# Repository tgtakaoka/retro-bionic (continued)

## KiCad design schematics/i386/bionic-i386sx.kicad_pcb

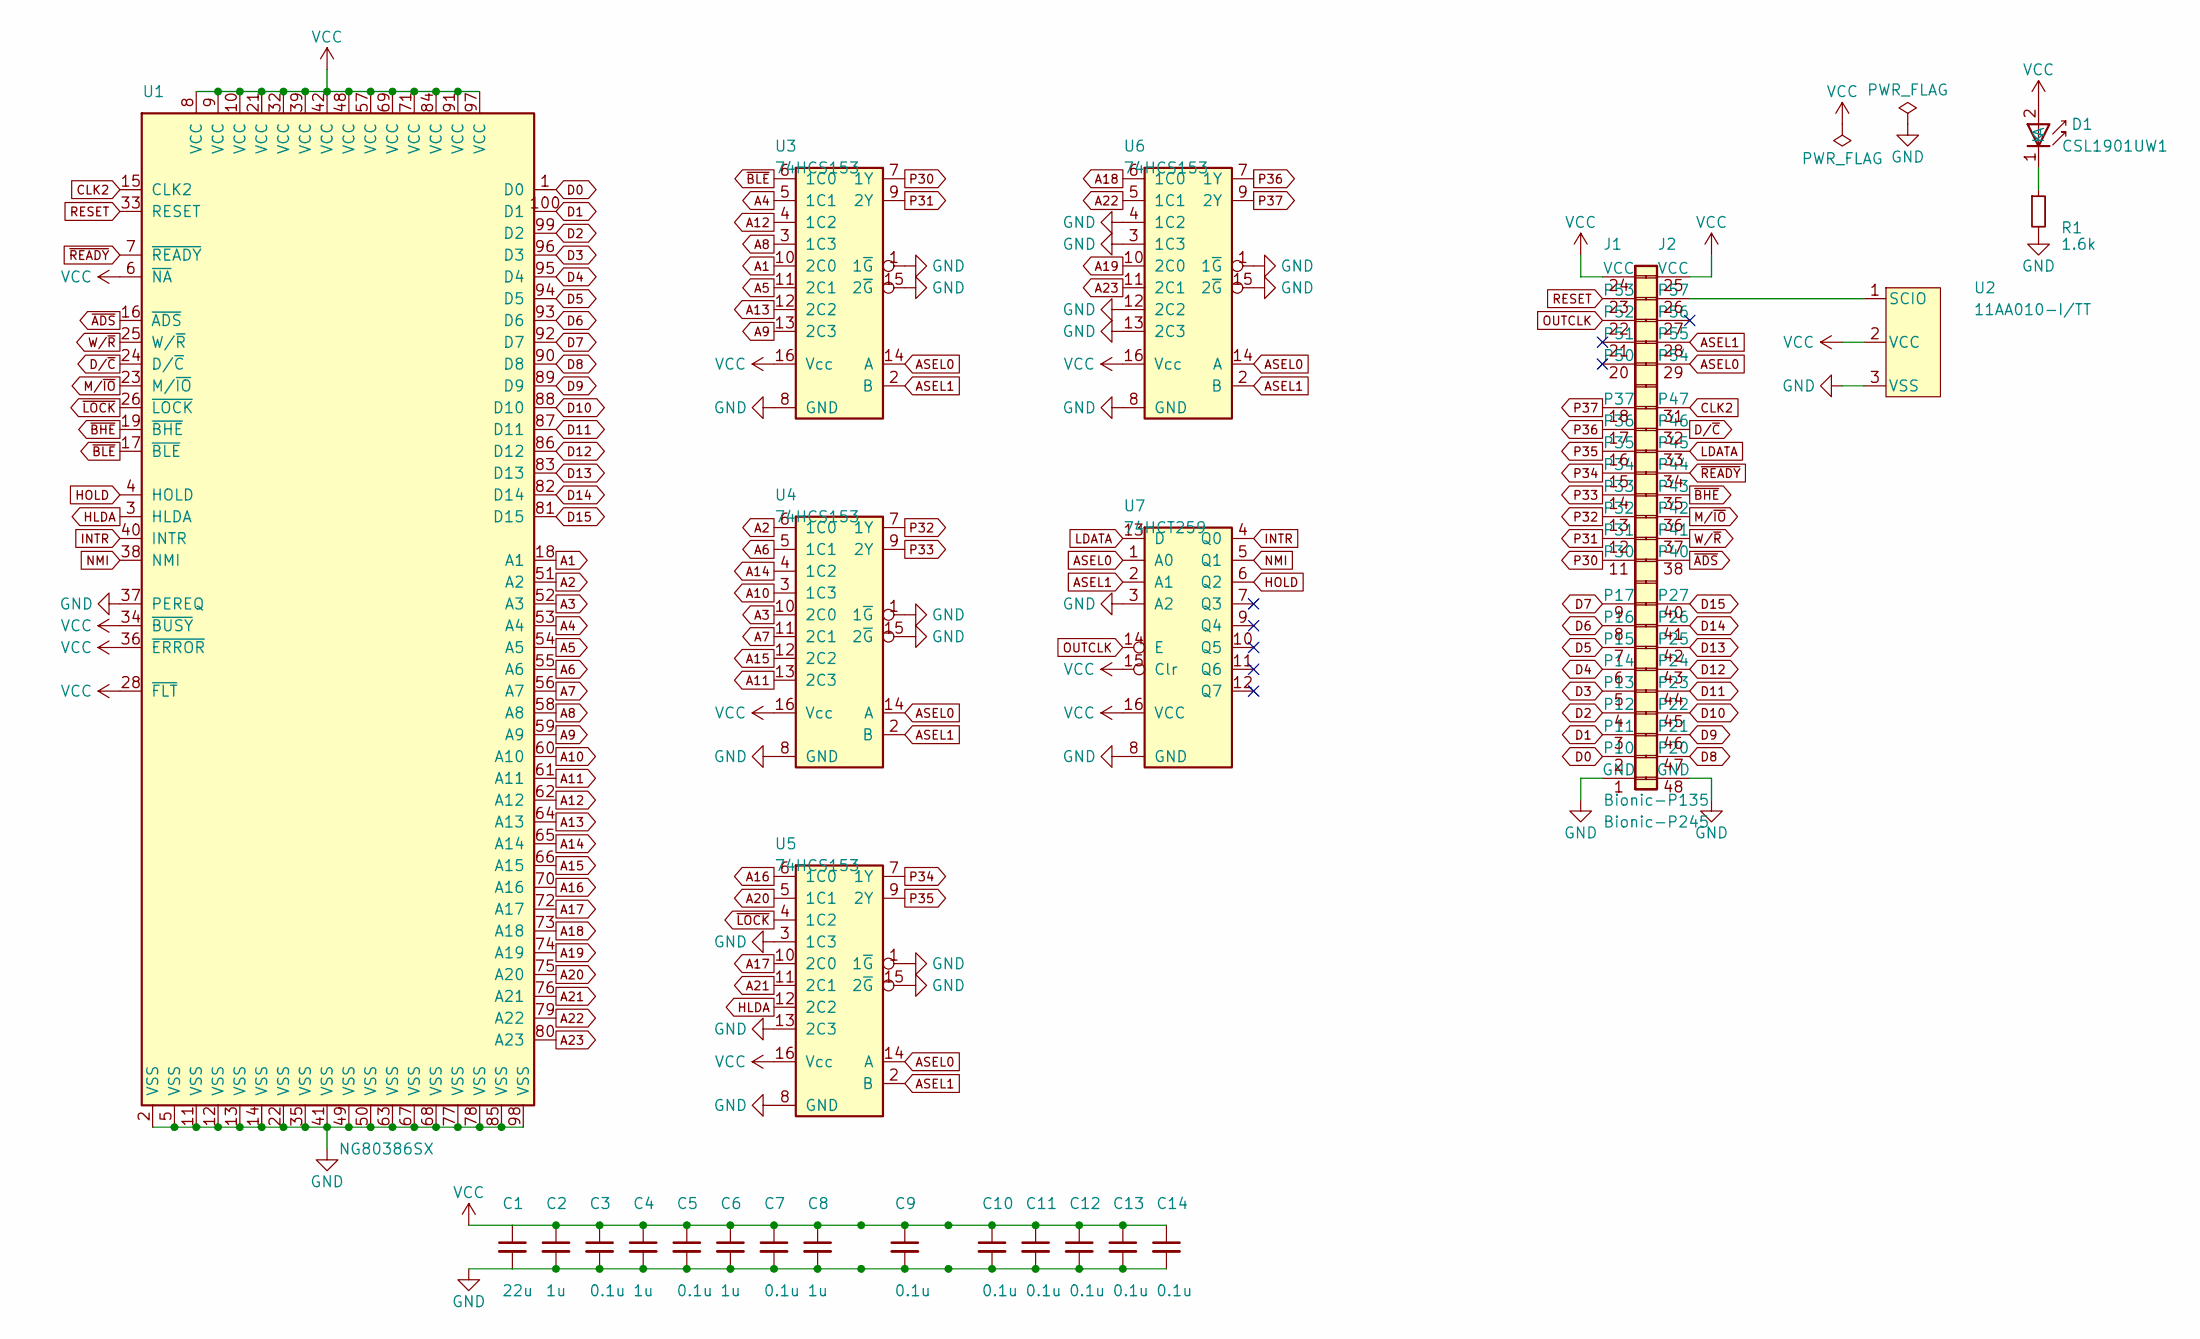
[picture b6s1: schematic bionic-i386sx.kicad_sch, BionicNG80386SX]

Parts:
C1: 22u; C_0603_1608Metric_Pad1.08x0.95mm_HandSolder
C2, C4, C6, C8: 1u; C_0603_1608Metric_Pad1.08x0.95mm_HandSolder
C3, C5, C7, C9, C10, C11, C12, C13, C14: 0.1u; C_0603_1608Metric_Pad1.08x0.95mm_HandSolder
D1: CSL1901UW1; LED_CSL1901UW1_ROM-M
J1: Bionic-P135; Bionic-P135_SMT
J2: Bionic-P245; Bionic-P245_SMT
R1: 1.6k; R_0603_1608Metric_Pad0.98x0.95mm_HandSolder
U1: NG80386SX; BQFP-100_19.05x19.05mm_P0.635mm
U2: 11AA010-I/TT; SOT-23_MC_MCH-M
U3, U4, U5, U6: 74HCS153; PW16-M
U7: 74HCT259; TSSOP16_SOT403-1_NEX-M

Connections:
A1: U1.18 (A1), U3.10 (2C0)
A2: U1.51 (A2), U4.6 (1C0)
A3: U1.52 (A3), U4.10 (2C0)
A4: U1.53 (A4), U3.5 (1C1)
A5: U1.54 (A5), U3.11 (2C1)
A6: U1.55 (A6), U4.5 (1C1)
A7: U1.56 (A7), U4.11 (2C1)
A8: U1.58 (A8), U3.3 (1C3)
A9: U1.59 (A9), U3.13 (2C3)
A10: U1.60 (A10), U4.3 (1C3)
A11: U1.61 (A11), U4.13 (2C3)
A12: U1.62 (A12), U3.4 (1C2)
A13: U1.64 (A13), U3.12 (2C2)
A14: U1.65 (A14), U4.4 (1C2)
A15: U1.66 (A15), U4.12 (2C2)
A16: U1.70 (A16), U5.6 (1C0)
A17: U1.72 (A17), U5.10 (2C0)
A18: U1.73 (A18), U6.6 (1C0)
A19: U1.74 (A19), U6.10 (2C0)
A20: U1.75 (A20), U5.5 (1C1)
A21: U1.76 (A21), U5.11 (2C1)
A22: U1.79 (A22), U6.5 (1C1)
A23: U1.80 (A23), U6.11 (2C1)
ASEL0: J2.29 (P54), U3.14 (A), U4.14 (A), U5.14 (A), U6.14 (A), U7.1 (A0)
ASEL1: J2.28 (P55), U3.2 (B), U4.2 (B), U5.2 (B), U6.2 (B), U7.2 (A1)
CLK2: J2.31 (P47), U1.15 (CLK2)
D0: J1.2 (P10), U1.1 (D0)
D1: J1.3 (P11), U1.100 (D1)
D2: J1.4 (P12), U1.99 (D2)
D3: J1.5 (P13), U1.96 (D3)
D4: J1.6 (P14), U1.95 (D4)
D5: J1.7 (P15), U1.94 (D5)
D6: J1.8 (P16), U1.93 (D6)
D7: J1.9 (P17), U1.92 (D7)
D8: J2.47 (P20), U1.90 (D8)
D9: J2.46 (P21), U1.89 (D9)
D10: J2.45 (P22), U1.88 (D10)
D11: J2.44 (P23), U1.87 (D11)
D12: J2.43 (P24), U1.86 (D12)
D13: J2.42 (P25), U1.83 (D13)
D14: J2.41 (P26), U1.82 (D14)
D15: J2.40 (P27), U1.81 (D15)
D/~C: J2.32 (P46), U1.24 (D/~C)
GND: C1.2, C2.2, C3.2, C4.2, C5.2, C6.2, C7.2, C8.2, C9.2, C10.2, C11.2, C12.2, C13.2, C14.2, J1.1 (GND), J2.48 (GND), R1.2, U1.2 (VSS), U1.5 (VSS), U1.11 (VSS), U1.12 (VSS), U1.13 (VSS), U1.14 (VSS), U1.22 (VSS), U1.35 (VSS), U1.37 (PEREQ), U1.41 (VSS), U1.49 (VSS), U1.50 (VSS), U1.63 (VSS), U1.67 (VSS), U1.68 (VSS), U1.77 (VSS), U1.78 (VSS), U1.85 (VSS), U1.98 (VSS), U2.3 (VSS), U3.1 (1~G), U3.8 (GND), U3.15 (2~G), U4.1 (1~G), U4.8 (GND), U4.15 (2~G), U5.1 (1~G), U5.3 (1C3), U5.8 (GND), U5.13 (2C3), U5.15 (2~G), U6.1 (1~G), U6.3 (1C3), U6.4 (1C2), U6.8 (GND), U6.12 (2C2), U6.13 (2C3), U6.15 (2~G), U7.3 (A2), U7.8 (GND)
HLDA: U1.3 (HLDA), U5.12 (2C2)
HOLD: U1.4 (HOLD), U7.6 (Q2)
INTR: U1.40 (INTR), U7.4 (Q0)
LDATA: J2.33 (P45), U7.13 (D)
M/~IO: J2.36 (P42), U1.23 (M/~IO)
NMI: U1.38 (NMI), U7.5 (Q1)
unnamed: D1.1 (K), R1.1
unnamed: J2.26 (P57), U2.1 (SCIO)
OUTCLK: J1.22 (P52), U7.14 (E)
P30: J1.11 (P30), U3.7 (1Y)
P31: J1.12 (P31), U3.9 (2Y)
P32: J1.13 (P32), U4.7 (1Y)
P33: J1.14 (P33), U4.9 (2Y)
P34: J1.15 (P34), U5.7 (1Y)
P35: J1.16 (P35), U5.9 (2Y)
P36: J1.17 (P36), U6.7 (1Y)
P37: J1.18 (P37), U6.9 (2Y)
RESET: J1.23 (P53), U1.33 (RESET)
VCC: C1.1, C2.1, C3.1, C4.1, C5.1, C6.1, C7.1, C8.1, C9.1, C10.1, C11.1, C12.1, C13.1, C14.1, D1.2 (A), J1.24 (VCC), J2.25 (VCC), U1.6 (~NA), U1.8 (VCC), U1.9 (VCC), U1.10 (VCC), U1.21 (VCC), U1.28 (~FLT), U1.32 (VCC), U1.34 (~BUSY), U1.36 (~ERROR), U1.39 (VCC), U1.42 (VCC), U1.48 (VCC), U1.57 (VCC), U1.69 (VCC), U1.71 (VCC), U1.84 (VCC), U1.91 (VCC), U1.97 (VCC), U2.2 (VCC), U3.16 (Vcc), U4.16 (Vcc), U5.16 (Vcc), U6.16 (Vcc), U7.15 (Clr), U7.16 (VCC)
W/~R: J2.37 (P41), U1.25 (W/~R)
~ADS: J2.38 (P40), U1.16 (~ADS)
~BHE: J2.35 (P43), U1.19 (~BHE)
~BLE: U1.17 (~BLE), U3.6 (1C0)
~LOCK: U1.26 (~LOCK), U5.4 (1C2)
~READY: J2.34 (P44), U1.7 (~READY)

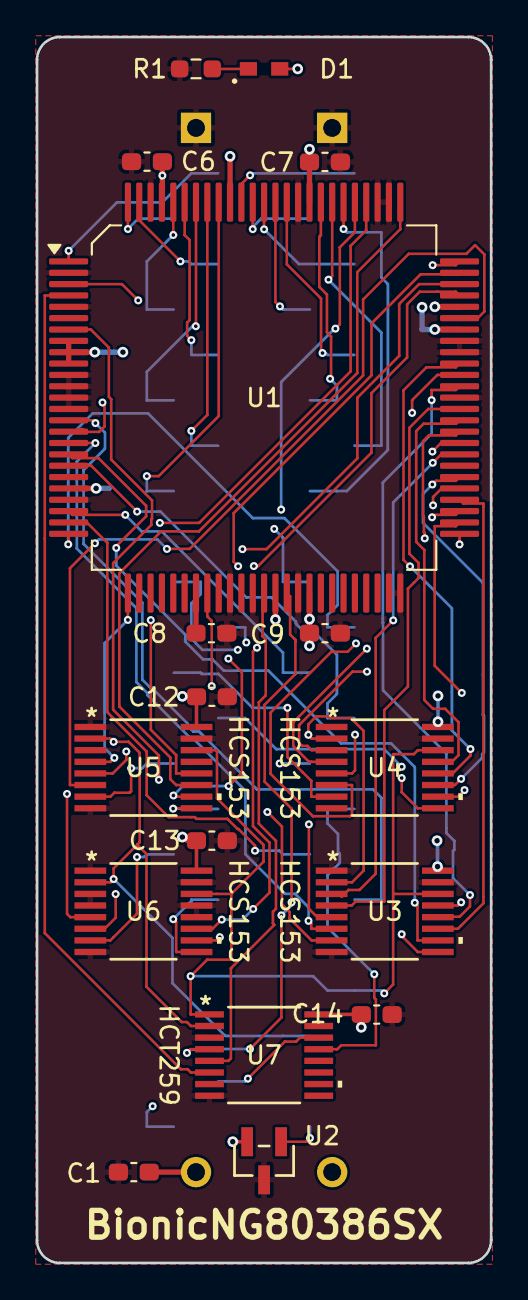
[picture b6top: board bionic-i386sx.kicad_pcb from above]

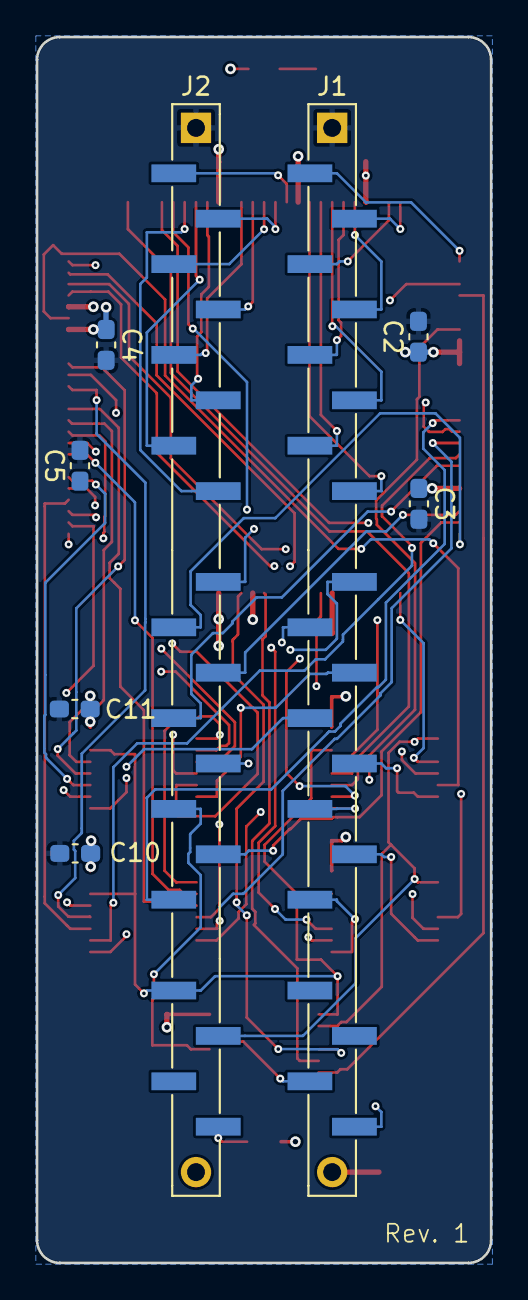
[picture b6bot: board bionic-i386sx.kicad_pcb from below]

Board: 4 copper layers, 25.4 x 68.6 mm, 25 parts (8 on the bottom side), 69 nets.

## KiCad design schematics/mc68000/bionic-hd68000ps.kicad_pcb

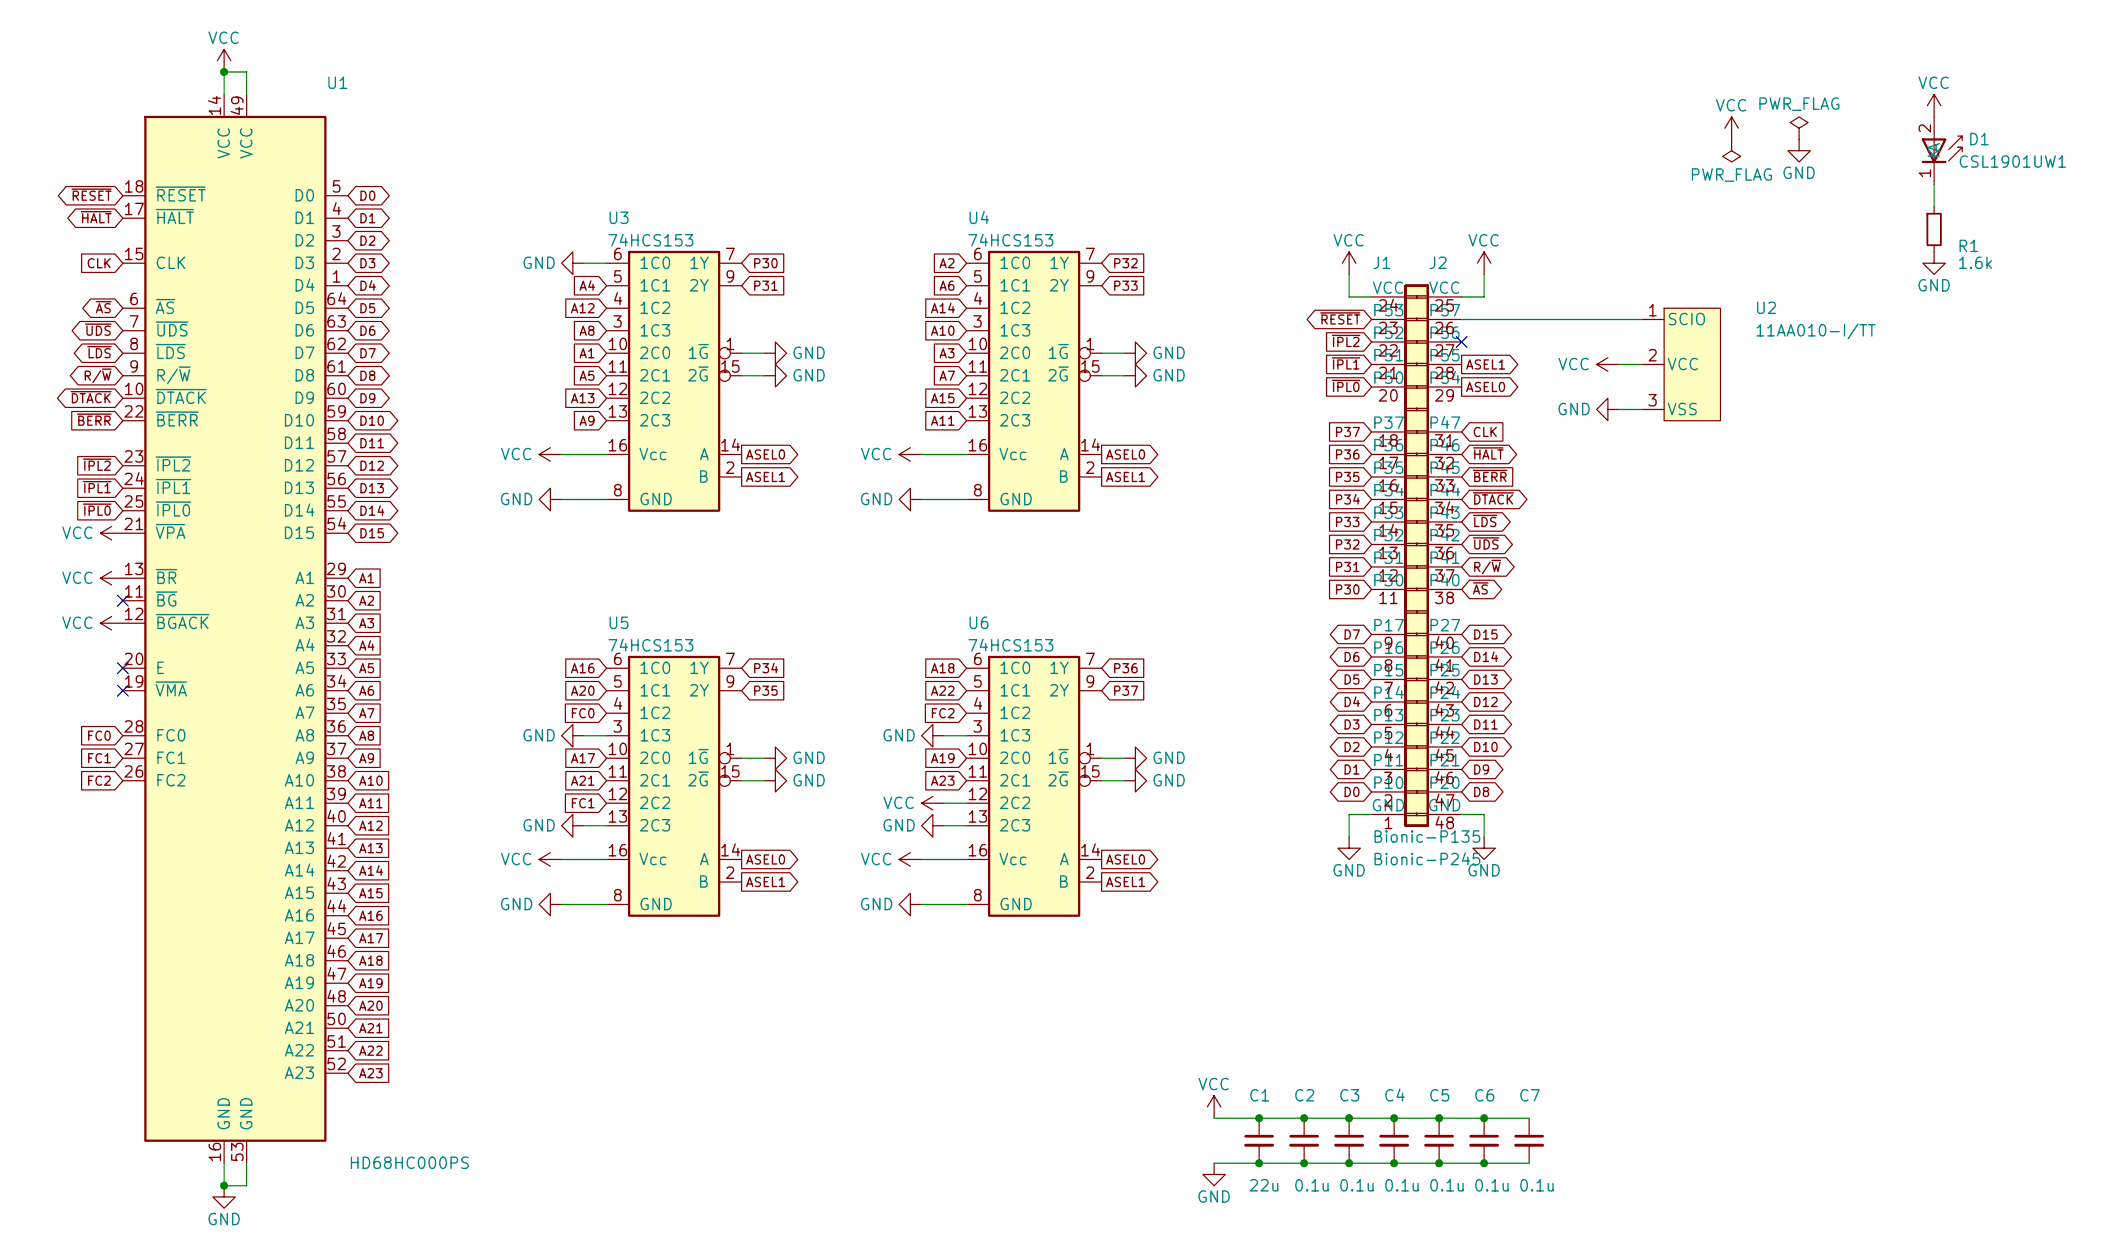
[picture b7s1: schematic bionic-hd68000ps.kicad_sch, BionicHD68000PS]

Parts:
C1: 22u; C_0603_1608Metric_Pad1.08x0.95mm_HandSolder
C2, C3, C4, C5, C6, C7: 0.1u; C_0603_1608Metric_Pad1.08x0.95mm_HandSolder
D1: CSL1901UW1; LED_CSL1901UW1_ROM-M
J1: Bionic-P135; Bionic-P135_SMT
J2: Bionic-P245; Bionic-P245_SMT
R1: 1.6k; R_0603_1608Metric_Pad0.98x0.95mm_HandSolder
U1: HD68HC000PS; SDIP-64_W19.05mm_Socket
U2: 11AA010-I/TT; SOT-23_MC_MCH-M
U3, U4, U5, U6: 74HCS153; PW16-M

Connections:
A1: U1.29 (A1), U3.10 (2C0)
A2: U1.30 (A2), U4.6 (1C0)
A3: U1.31 (A3), U4.10 (2C0)
A4: U1.32 (A4), U3.5 (1C1)
A5: U1.33 (A5), U3.11 (2C1)
A6: U1.34 (A6), U4.5 (1C1)
A7: U1.35 (A7), U4.11 (2C1)
A8: U1.36 (A8), U3.3 (1C3)
A9: U1.37 (A9), U3.13 (2C3)
A10: U1.38 (A10), U4.3 (1C3)
A11: U1.39 (A11), U4.13 (2C3)
A12: U1.40 (A12), U3.4 (1C2)
A13: U1.41 (A13), U3.12 (2C2)
A14: U1.42 (A14), U4.4 (1C2)
A15: U1.43 (A15), U4.12 (2C2)
A16: U1.44 (A16), U5.6 (1C0)
A17: U1.45 (A17), U5.10 (2C0)
A18: U1.46 (A18), U6.6 (1C0)
A19: U1.47 (A19), U6.10 (2C0)
A20: U1.48 (A20), U5.5 (1C1)
A21: U1.50 (A21), U5.11 (2C1)
A22: U1.51 (A22), U6.5 (1C1)
A23: U1.52 (A23), U6.11 (2C1)
ASEL0: J2.29 (P54), U3.14 (A), U4.14 (A), U5.14 (A), U6.14 (A)
ASEL1: J2.28 (P55), U3.2 (B), U4.2 (B), U5.2 (B), U6.2 (B)
CLK: J2.31 (P47), U1.15 (CLK)
D0: J1.2 (P10), U1.5 (D0)
D1: J1.3 (P11), U1.4 (D1)
D2: J1.4 (P12), U1.3 (D2)
D3: J1.5 (P13), U1.2 (D3)
D4: J1.6 (P14), U1.1 (D4)
D5: J1.7 (P15), U1.64 (D5)
D6: J1.8 (P16), U1.63 (D6)
D7: J1.9 (P17), U1.62 (D7)
D8: J2.47 (P20), U1.61 (D8)
D9: J2.46 (P21), U1.60 (D9)
D10: J2.45 (P22), U1.59 (D10)
D11: J2.44 (P23), U1.58 (D11)
D12: J2.43 (P24), U1.57 (D12)
D13: J2.42 (P25), U1.56 (D13)
D14: J2.41 (P26), U1.55 (D14)
D15: J2.40 (P27), U1.54 (D15)
FC0: U1.28 (FC0), U5.4 (1C2)
FC1: U1.27 (FC1), U5.12 (2C2)
FC2: U1.26 (FC2), U6.4 (1C2)
GND: C1.2, C2.2, C3.2, C4.2, C5.2, C6.2, C7.2, J1.1 (GND), J2.48 (GND), R1.2, U1.16 (GND), U1.53 (GND), U2.3 (VSS), U3.1 (1~G), U3.6 (1C0), U3.8 (GND), U3.15 (2~G), U4.1 (1~G), U4.8 (GND), U4.15 (2~G), U5.1 (1~G), U5.3 (1C3), U5.8 (GND), U5.13 (2C3), U5.15 (2~G), U6.1 (1~G), U6.3 (1C3), U6.8 (GND), U6.13 (2C3), U6.15 (2~G)
unnamed: D1.1 (K), R1.1
unnamed: J2.26 (P57), U2.1 (SCIO)
P30: J1.11 (P30), U3.7 (1Y)
P31: J1.12 (P31), U3.9 (2Y)
P32: J1.13 (P32), U4.7 (1Y)
P33: J1.14 (P33), U4.9 (2Y)
P34: J1.15 (P34), U5.7 (1Y)
P35: J1.16 (P35), U5.9 (2Y)
P36: J1.17 (P36), U6.7 (1Y)
P37: J1.18 (P37), U6.9 (2Y)
R/~W: J2.37 (P41), U1.9 (R/~W)
VCC: C1.1, C2.1, C3.1, C4.1, C5.1, C6.1, C7.1, D1.2 (A), J1.24 (VCC), J2.25 (VCC), U1.12 (~BGACK), U1.13 (~BR), U1.14 (VCC), U1.21 (~VPA), U1.49 (VCC), U2.2 (VCC), U3.16 (Vcc), U4.16 (Vcc), U5.16 (Vcc), U6.12 (2C2), U6.16 (Vcc)
~AS: J2.38 (P40), U1.6 (~AS)
~BERR: J2.33 (P45), U1.22 (~BERR)
~DTACK: J2.34 (P44), U1.10 (~DTACK)
~HALT: J2.32 (P46), U1.17 (~HALT)
~IPL0: J1.20 (P50), U1.25 (~IPL0)
~IPL1: J1.21 (P51), U1.24 (~IPL1)
~IPL2: J1.22 (P52), U1.23 (~IPL2)
~LDS: J2.35 (P43), U1.8 (~LDS)
~RESET: J1.23 (P53), U1.18 (~RESET)
~UDS: J2.36 (P42), U1.7 (~UDS)

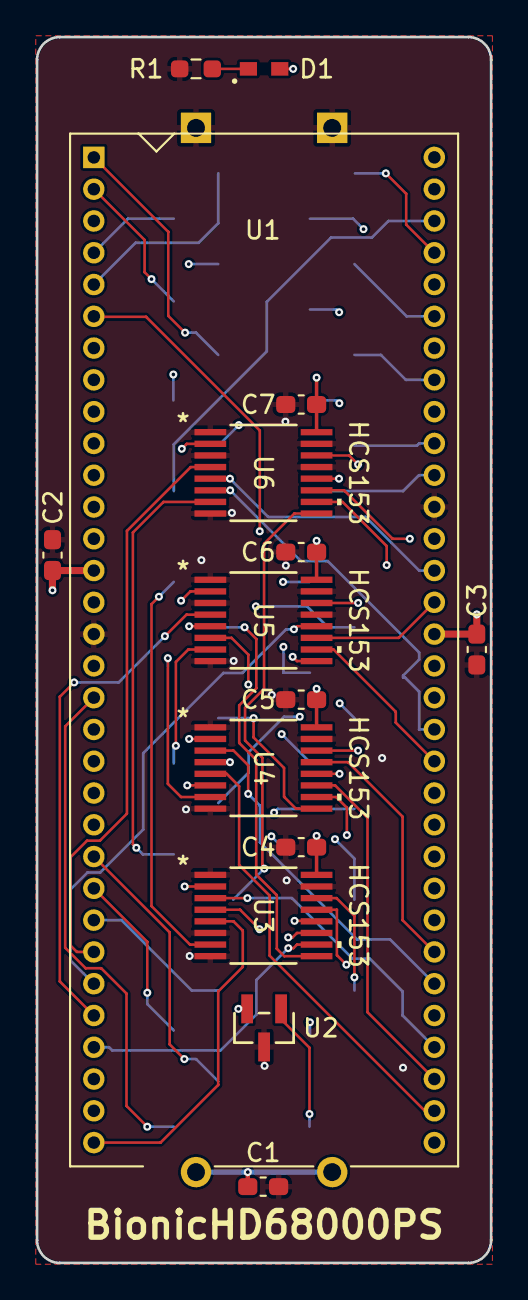
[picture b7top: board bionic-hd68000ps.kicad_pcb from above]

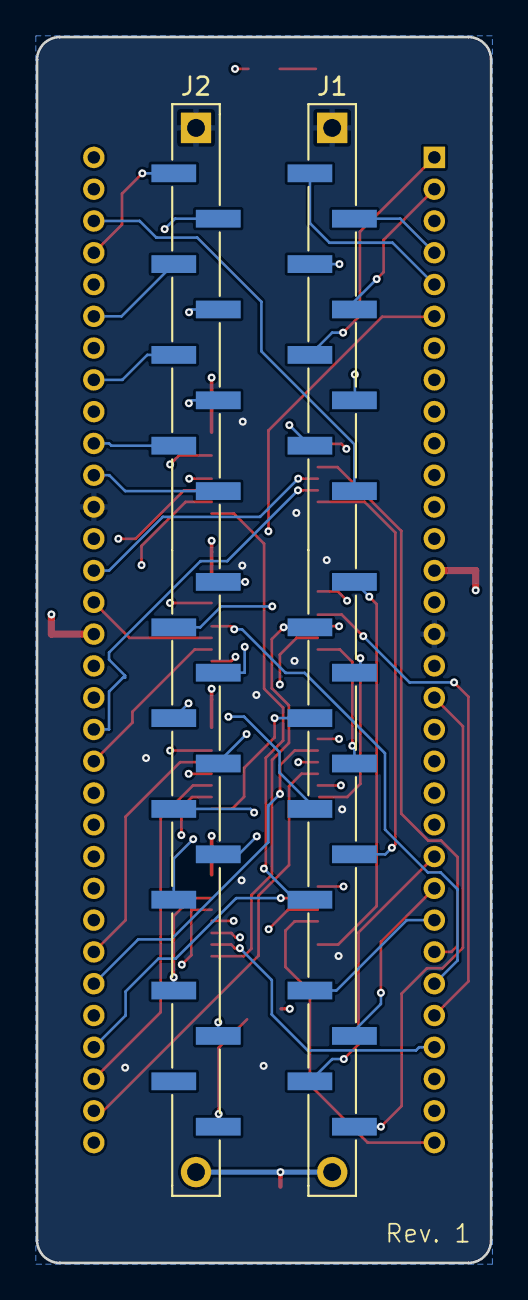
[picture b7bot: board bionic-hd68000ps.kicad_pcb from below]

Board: 4 copper layers, 25.4 x 68.6 mm, 17 parts (2 on the bottom side), 68 nets.

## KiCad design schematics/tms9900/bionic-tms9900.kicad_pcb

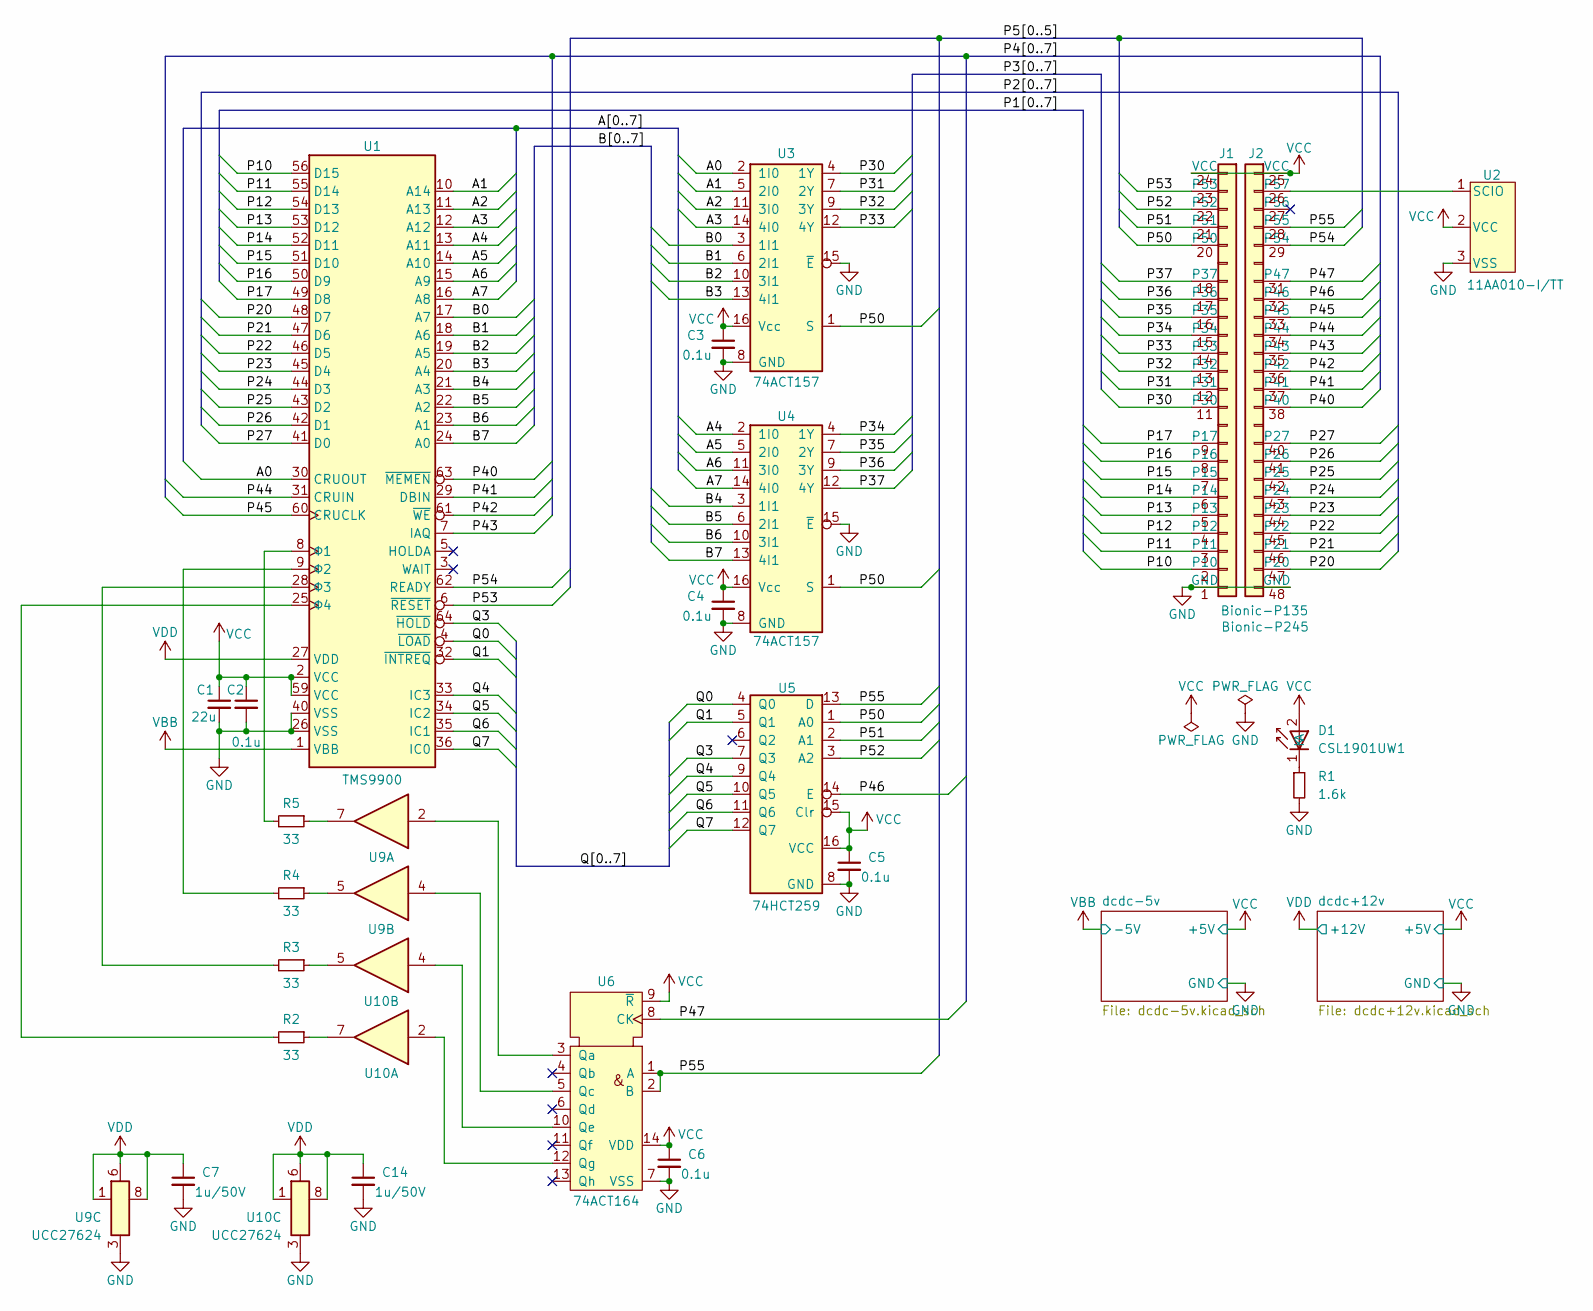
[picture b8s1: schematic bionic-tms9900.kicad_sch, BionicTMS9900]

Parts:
C1: 22u; C_0603_1608Metric_Pad1.08x0.95mm_HandSolder
C2, C3, C4, C5, C6: 0.1u; C_0603_1608Metric_Pad1.08x0.95mm_HandSolder
C7, C14: 1u/50V; C_0603_1608Metric_Pad1.08x0.95mm_HandSolder
D1: CSL1901UW1; LED_CSL1901UW1_ROM-M
J1: Bionic-P135; Bionic-P135_SMT
J2: Bionic-P245; Bionic-P245_SMT
R1: 1.6k; R_0603_1608Metric_Pad0.98x0.95mm_HandSolder
R2, R3, R4, R5: 33; R_0603_1608Metric_Pad0.98x0.95mm_HandSolder
U1: TMS9900; DIP-64_W22.86mm_Socket
U2: 11AA010-I/TT; SOT-23_MC_MCH-M
U3, U4: 74ACT157; PW16-M
U5: 74HCT259; TSSOP16_SOT403-1_NEX-M
U6: 74ACT164; PW14-M
U9, U10: UCC27624; DGN8-M

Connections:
/A0: U1.30 (CRUOUT), U3.2 (1I0)
/A1: U1.10 (A14), U3.5 (2I0)
/A2: U1.11 (A13), U3.11 (3I0)
/A3: U1.12 (A12), U3.14 (4I0)
/A4: U1.13 (A11), U4.2 (1I0)
/A5: U1.14 (A10), U4.5 (2I0)
/A6: U1.15 (A9), U4.11 (3I0)
/A7: U1.16 (A8), U4.14 (4I0)
/B0: U1.17 (A7), U3.3 (1I1)
/B1: U1.18 (A6), U3.6 (2I1)
/B2: U1.19 (A5), U3.10 (3I1)
/B3: U1.20 (A4), U3.13 (4I1)
/B4: U1.21 (A3), U4.3 (1I1)
/B5: U1.22 (A2), U4.6 (2I1)
/B6: U1.23 (A1), U4.10 (3I1)
/B7: U1.24 (A0), U4.13 (4I1)
/P10: J1.2 (P10), U1.56 (D15)
/P11: J1.3 (P11), U1.55 (D14)
/P12: J1.4 (P12), U1.54 (D13)
/P13: J1.5 (P13), U1.53 (D12)
/P14: J1.6 (P14), U1.52 (D11)
/P15: J1.7 (P15), U1.51 (D10)
/P16: J1.8 (P16), U1.50 (D9)
/P17: J1.9 (P17), U1.49 (D8)
/P20: J2.47 (P20), U1.48 (D7)
/P21: J2.46 (P21), U1.47 (D6)
/P22: J2.45 (P22), U1.46 (D5)
/P23: J2.44 (P23), U1.45 (D4)
/P24: J2.43 (P24), U1.44 (D3)
/P25: J2.42 (P25), U1.43 (D2)
/P26: J2.41 (P26), U1.42 (D1)
/P27: J2.40 (P27), U1.41 (D0)
/P30: J1.11 (P30), U3.4 (1Y)
/P31: J1.12 (P31), U3.7 (2Y)
/P32: J1.13 (P32), U3.9 (3Y)
/P33: J1.14 (P33), U3.12 (4Y)
/P34: J1.15 (P34), U4.4 (1Y)
/P35: J1.16 (P35), U4.7 (2Y)
/P36: J1.17 (P36), U4.9 (3Y)
/P37: J1.18 (P37), U4.12 (4Y)
/P40: J2.38 (P40), U1.63 (~MEMEN)
/P41: J2.37 (P41), U1.29 (DBIN)
/P42: J2.36 (P42), U1.61 (~WE)
/P43: J2.35 (P43), U1.7 (IAQ)
/P44: J2.34 (P44), U1.31 (CRUIN)
/P45: J2.33 (P45), U1.60 (CRUCLK)
/P46: J2.32 (P46), U5.14 (E)
/P47: J2.31 (P47), U6.8 (CK)
/P50: J1.20 (P50), U3.1 (S), U4.1 (S), U5.1 (A0)
/P51: J1.21 (P51), U5.2 (A1)
/P52: J1.22 (P52), U5.3 (A2)
/P53: J1.23 (P53), U1.6 (~RESET)
/P54: J2.29 (P54), U1.62 (READY)
/P55: J2.28 (P55), U5.13 (D), U6.1 (A), U6.2 (B)
/Q0: U1.4 (~LOAD), U5.4 (Q0)
/Q1: U1.32 (~INTREQ), U5.5 (Q1)
/Q3: U1.64 (~HOLD), U5.7 (Q3)
/Q4: U1.33 (IC3), U5.9 (Q4)
/Q5: U1.34 (IC2), U5.10 (Q5)
/Q6: U1.35 (IC1), U5.11 (Q6)
/Q7: U1.36 (IC0), U5.12 (Q7)
GND: C1.2, C2.2, C3.2, C4.2, C5.2, C6.2, C7.2, C14.2, J1.1 (GND), J2.48 (GND), R1.2, U1.26 (VSS), U1.40 (VSS), U2.3 (VSS), U3.8 (GND), U3.15 (~E), U4.8 (GND), U4.15 (~E), U5.8 (GND), U6.7 (VSS), U9.3 (GND), U10.3 (GND); also elsewhere on the board
unnamed: D1.1 (K), R1.1
unnamed: J2.26 (P57), U2.1 (SCIO)
unnamed: R5.2, U1.8 (Φ1)
unnamed: R4.2, U1.9 (Φ2)
unnamed: R3.2, U1.28 (Φ3)
unnamed: R2.2, U1.25 (Φ4)
unnamed: U6.3 (Qa), U9.2 (INA)
unnamed: U6.5 (Qc), U9.4 (INB)
unnamed: R5.1, U9.7 (OUTA)
unnamed: R4.1, U9.5 (OUTB)
unnamed: U6.12 (Qg), U10.2 (INA)
unnamed: R2.1, U10.7 (OUTA)
unnamed: U6.10 (Qe), U10.4 (INB)
unnamed: R3.1, U10.5 (OUTB)
VBB: U1.1 (VBB); also elsewhere on the board
VCC: C1.1, C2.1, C3.1, C4.1, C5.1, C6.1, D1.2 (A), J1.24 (VCC), J2.25 (VCC), U1.2 (VCC), U1.59 (VCC), U2.2 (VCC), U3.16 (Vcc), U4.16 (Vcc), U5.15 (Clr), U5.16 (VCC), U6.9 (~R), U6.14 (VDD); also elsewhere on the board
VDD: C7.1, C14.1, U1.27 (VDD), U9.1 (ENA), U9.6 (VDD), U9.8 (ENB), U10.1 (ENA), U10.6 (VDD), U10.8 (ENB); also elsewhere on the board

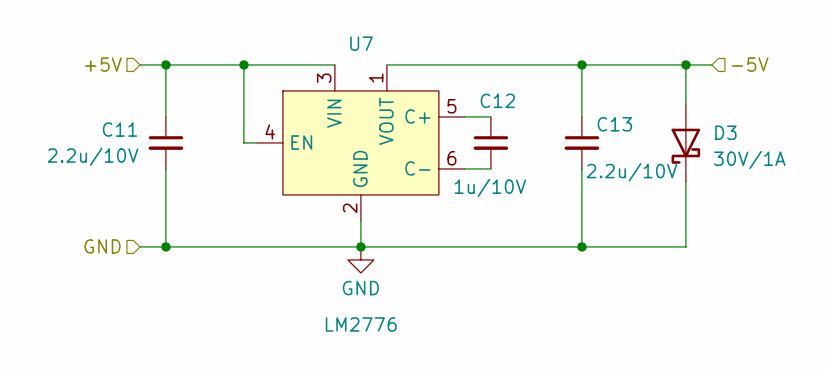
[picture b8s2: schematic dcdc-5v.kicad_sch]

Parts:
C11, C13: 2.2u/10V; C_0603_1608Metric_Pad1.08x0.95mm_HandSolder
C12: 1u/10V; C_0603_1608Metric_Pad1.08x0.95mm_HandSolder
D3: 30V/1A; CR_60M-60_ROM-M
U7: LM2776; DBV0006A_M

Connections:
GND: C11.2, C13.2, D3.1 (K), U7.2 (GND); also elsewhere on the board
unnamed: C12.1, U7.5 (C+)
unnamed: C12.2, U7.6 (C-)
VBB: C13.1, D3.2 (A), U7.1 (VOUT); also elsewhere on the board
VCC: C11.1, U7.3 (VIN), U7.4 (EN); also elsewhere on the board

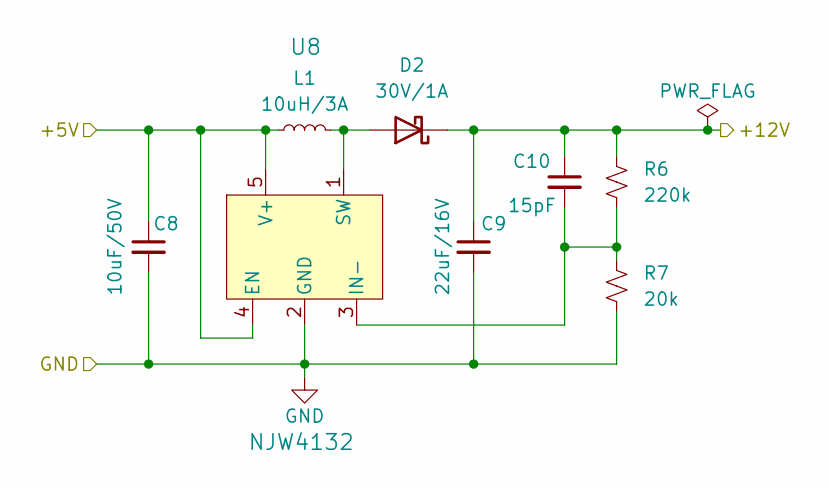
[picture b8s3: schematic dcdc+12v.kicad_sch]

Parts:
C8: 10uF/50V; C_0603_1608Metric_Pad1.08x0.95mm_HandSolder
C9: 22uF/16V; C_0603_1608Metric_Pad1.08x0.95mm_HandSolder
C10: 15pF; C_0603_1608Metric_Pad1.08x0.95mm_HandSolder
D2: 30V/1A; CR_60M-60_ROM-M
L1: 10uH/3A; IND_DFE322512F_MUR-M
R6: 220k; R_0603_1608Metric_Pad0.98x0.95mm_HandSolder
R7: 20k; R_0603_1608Metric_Pad0.98x0.95mm_HandSolder
U8: NJW4132; SOT-89-5_NMD-M

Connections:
GND: C8.2, C9.2, R7.2, U8.2 (GND); also elsewhere on the board
unnamed: D2.2 (A), L1.2, U8.1 (SW)
unnamed: C10.2, R6.2, R7.1, U8.3 (IN-)
VCC: C8.1, L1.1, U8.4 (EN), U8.5 (V+); also elsewhere on the board
VDD: C9.1, C10.1, D2.1 (K), R6.1; also elsewhere on the board

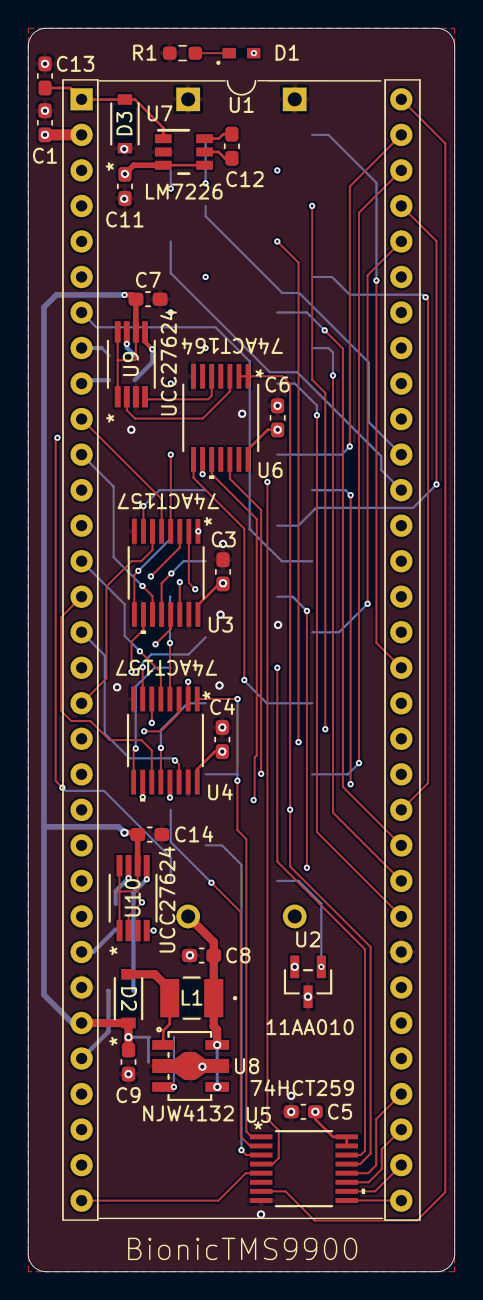
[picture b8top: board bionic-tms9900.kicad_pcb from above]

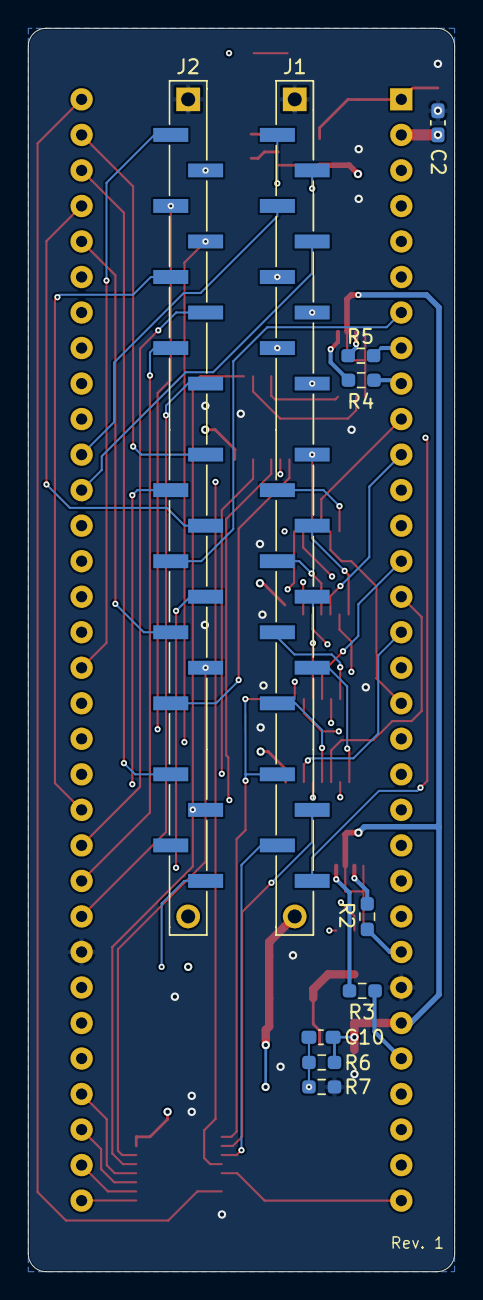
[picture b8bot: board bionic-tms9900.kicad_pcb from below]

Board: 4 copper layers, 30.5 x 88.9 mm, 37 parts (10 on the bottom side), 83 nets.
